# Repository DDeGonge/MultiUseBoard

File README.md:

# MultiUseBoard
The MUB - An ultra-compact, modular processing unit

## What is it?
A tiny, modular, all-in-one processing board. On it's own, it can't do much. But this board can be integrated into just about any other board. All of the mcu pins and power lines are accessible through the low-profile connectors, providing the maximum mcu potential for any project.

## So what makes this better than an Arduino/Blue Pill/Feather?
Well, a few reasons...
- Super compact 32mm x 23mm size
- Powerful Cortex M4 120MHz mcu
- Access to EVERY SINGLE PIN (41 total GPIO)
- Super tiny and low profile board-board connectors
- Onboard 5v and 3v3 regulators (Supports up to 32V input)
- $10 BOM cost at qty 1, $7 at qty 10
- Broken out programming header for easy access

## Cool, I want one!
Great! Then build it yourself :) I hope to sell these boards once the global chip shortage resolves itself, but for now you are on your own!

The gerber files to order the board are found in this repo. Order at your own risk.

A probably up-to-date BOM can be found [here](https://octopart.com/bom-tool/H8oUqADt)

A custom package for kicad exists in the libraries folder, so you can easily integrate the mounting footprint into your own board and simply connect a MUB in the slot.

Godspeed.

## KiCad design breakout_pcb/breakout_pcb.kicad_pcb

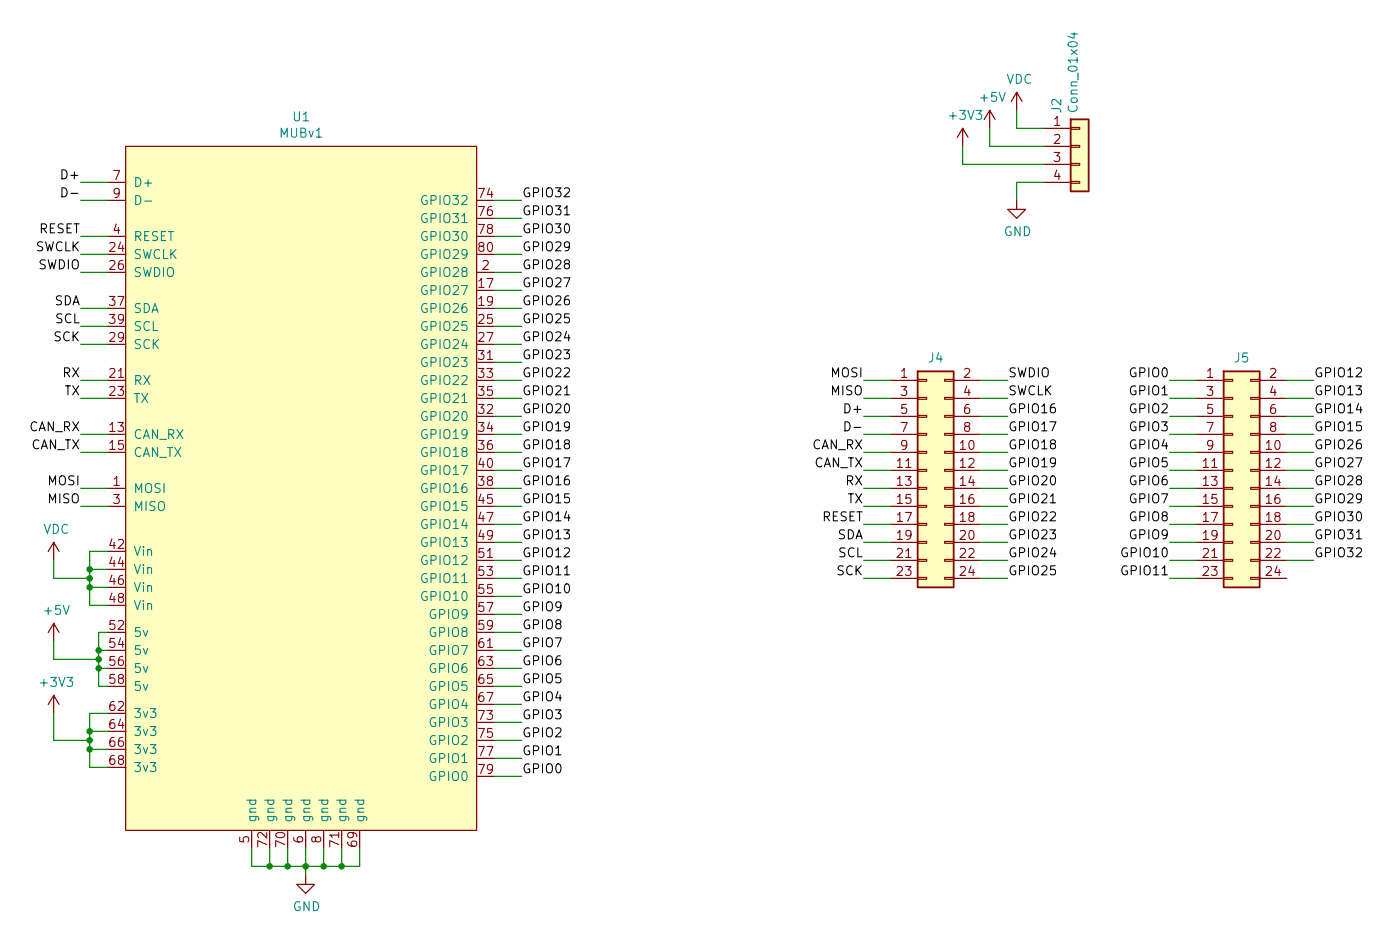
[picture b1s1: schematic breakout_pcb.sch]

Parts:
J2: Conn_01x04; PinSocket_1x04_P2.54mm_Vertical
J4, J5: Conn_02x12_Odd_Even; PinSocket_2x12_P2.54mm_Vertical
U1: MUBv1; MUB_v1

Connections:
+3V3: J2.3, U1.62 (3v3), U1.64 (3v3), U1.66 (3v3), U1.68 (3v3)
+5V: J2.2, U1.52 (5v), U1.54 (5v), U1.56 (5v), U1.58 (5v)
/CAN_RX: J4.9, U1.13 (CAN_RX)
/CAN_TX: J4.11, U1.15 (CAN_TX)
/D+: J4.5, U1.7 (D+)
/D-: J4.7, U1.9 (D-)
/GPIO0: J5.1, U1.79 (GPIO0)
/GPIO1: J5.3, U1.77 (GPIO1)
/GPIO2: J5.5, U1.75 (GPIO2)
/GPIO3: J5.7, U1.73 (GPIO3)
/GPIO4: J5.9, U1.67 (GPIO4)
/GPIO5: J5.11, U1.65 (GPIO5)
/GPIO6: J5.13, U1.63 (GPIO6)
/GPIO7: J5.15, U1.61 (GPIO7)
/GPIO8: J5.17, U1.59 (GPIO8)
/GPIO9: J5.19, U1.57 (GPIO9)
/GPIO10: J5.21, U1.55 (GPIO10)
/GPIO11: J5.23, U1.53 (GPIO11)
/GPIO12: J5.2, U1.51 (GPIO12)
/GPIO13: J5.4, U1.49 (GPIO13)
/GPIO14: J5.6, U1.47 (GPIO14)
/GPIO15: J5.8, U1.45 (GPIO15)
/GPIO16: J4.6, U1.38 (GPIO16)
/GPIO17: J4.8, U1.40 (GPIO17)
/GPIO18: J4.10, U1.36 (GPIO18)
/GPIO19: J4.12, U1.34 (GPIO19)
/GPIO20: J4.14, U1.32 (GPIO20)
/GPIO21: J4.16, U1.35 (GPIO21)
/GPIO22: J4.18, U1.33 (GPIO22)
/GPIO23: J4.20, U1.31 (GPIO23)
/GPIO24: J4.22, U1.27 (GPIO24)
/GPIO25: J4.24, U1.25 (GPIO25)
/GPIO26: J5.10, U1.19 (GPIO26)
/GPIO27: J5.12, U1.17 (GPIO27)
/GPIO28: J5.14, U1.2 (GPIO28)
/GPIO29: J5.16, U1.80 (GPIO29)
/GPIO30: J5.18, U1.78 (GPIO30)
/GPIO31: J5.20, U1.76 (GPIO31)
/GPIO32: J5.22, U1.74 (GPIO32)
/MISO: J4.3, U1.3 (MISO)
/MOSI: J4.1, U1.1 (MOSI)
/RESET: J4.17, U1.4 (RESET)
/RX: J4.13, U1.21 (RX)
/SCK: J4.23, U1.29 (SCK)
/SCL: J4.21, U1.39 (SCL)
/SDA: J4.19, U1.37 (SDA)
/SWCLK: J4.4, U1.24 (SWCLK)
/SWDIO: J4.2, U1.26 (SWDIO)
/TX: J4.15, U1.23 (TX)
GND: J2.4, U1.5 (gnd), U1.6 (gnd), U1.8 (gnd), U1.69 (gnd), U1.70 (gnd), U1.71 (gnd), U1.72 (gnd)
VDC: J2.1, U1.42 (Vin), U1.44 (Vin), U1.46 (Vin), U1.48 (Vin)

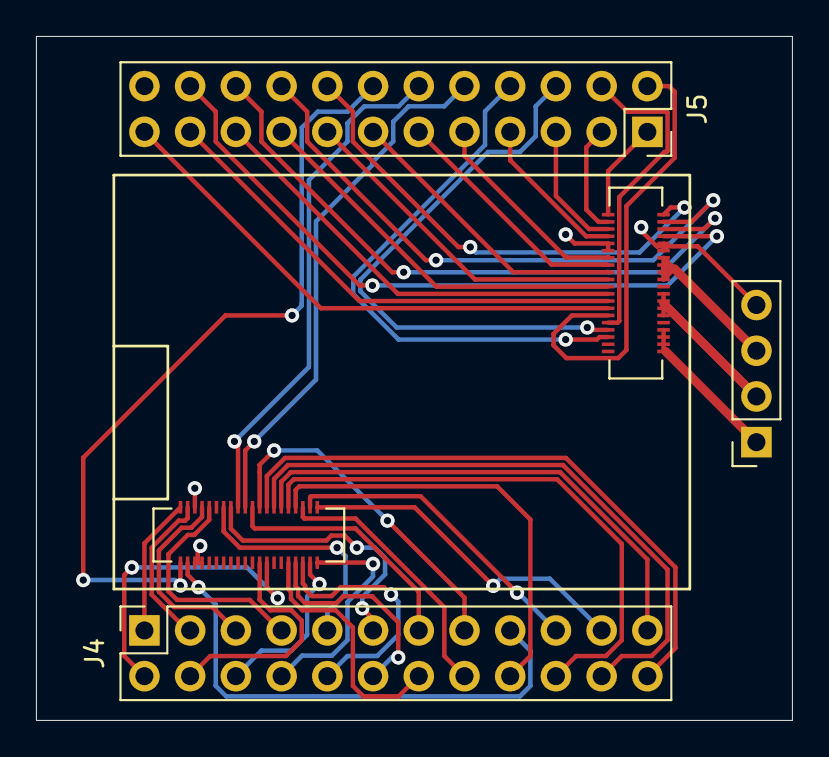
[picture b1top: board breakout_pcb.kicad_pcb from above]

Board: 2 copper layers, 42.0 x 38.0 mm, 4 parts (0 on the bottom side), 51 nets.

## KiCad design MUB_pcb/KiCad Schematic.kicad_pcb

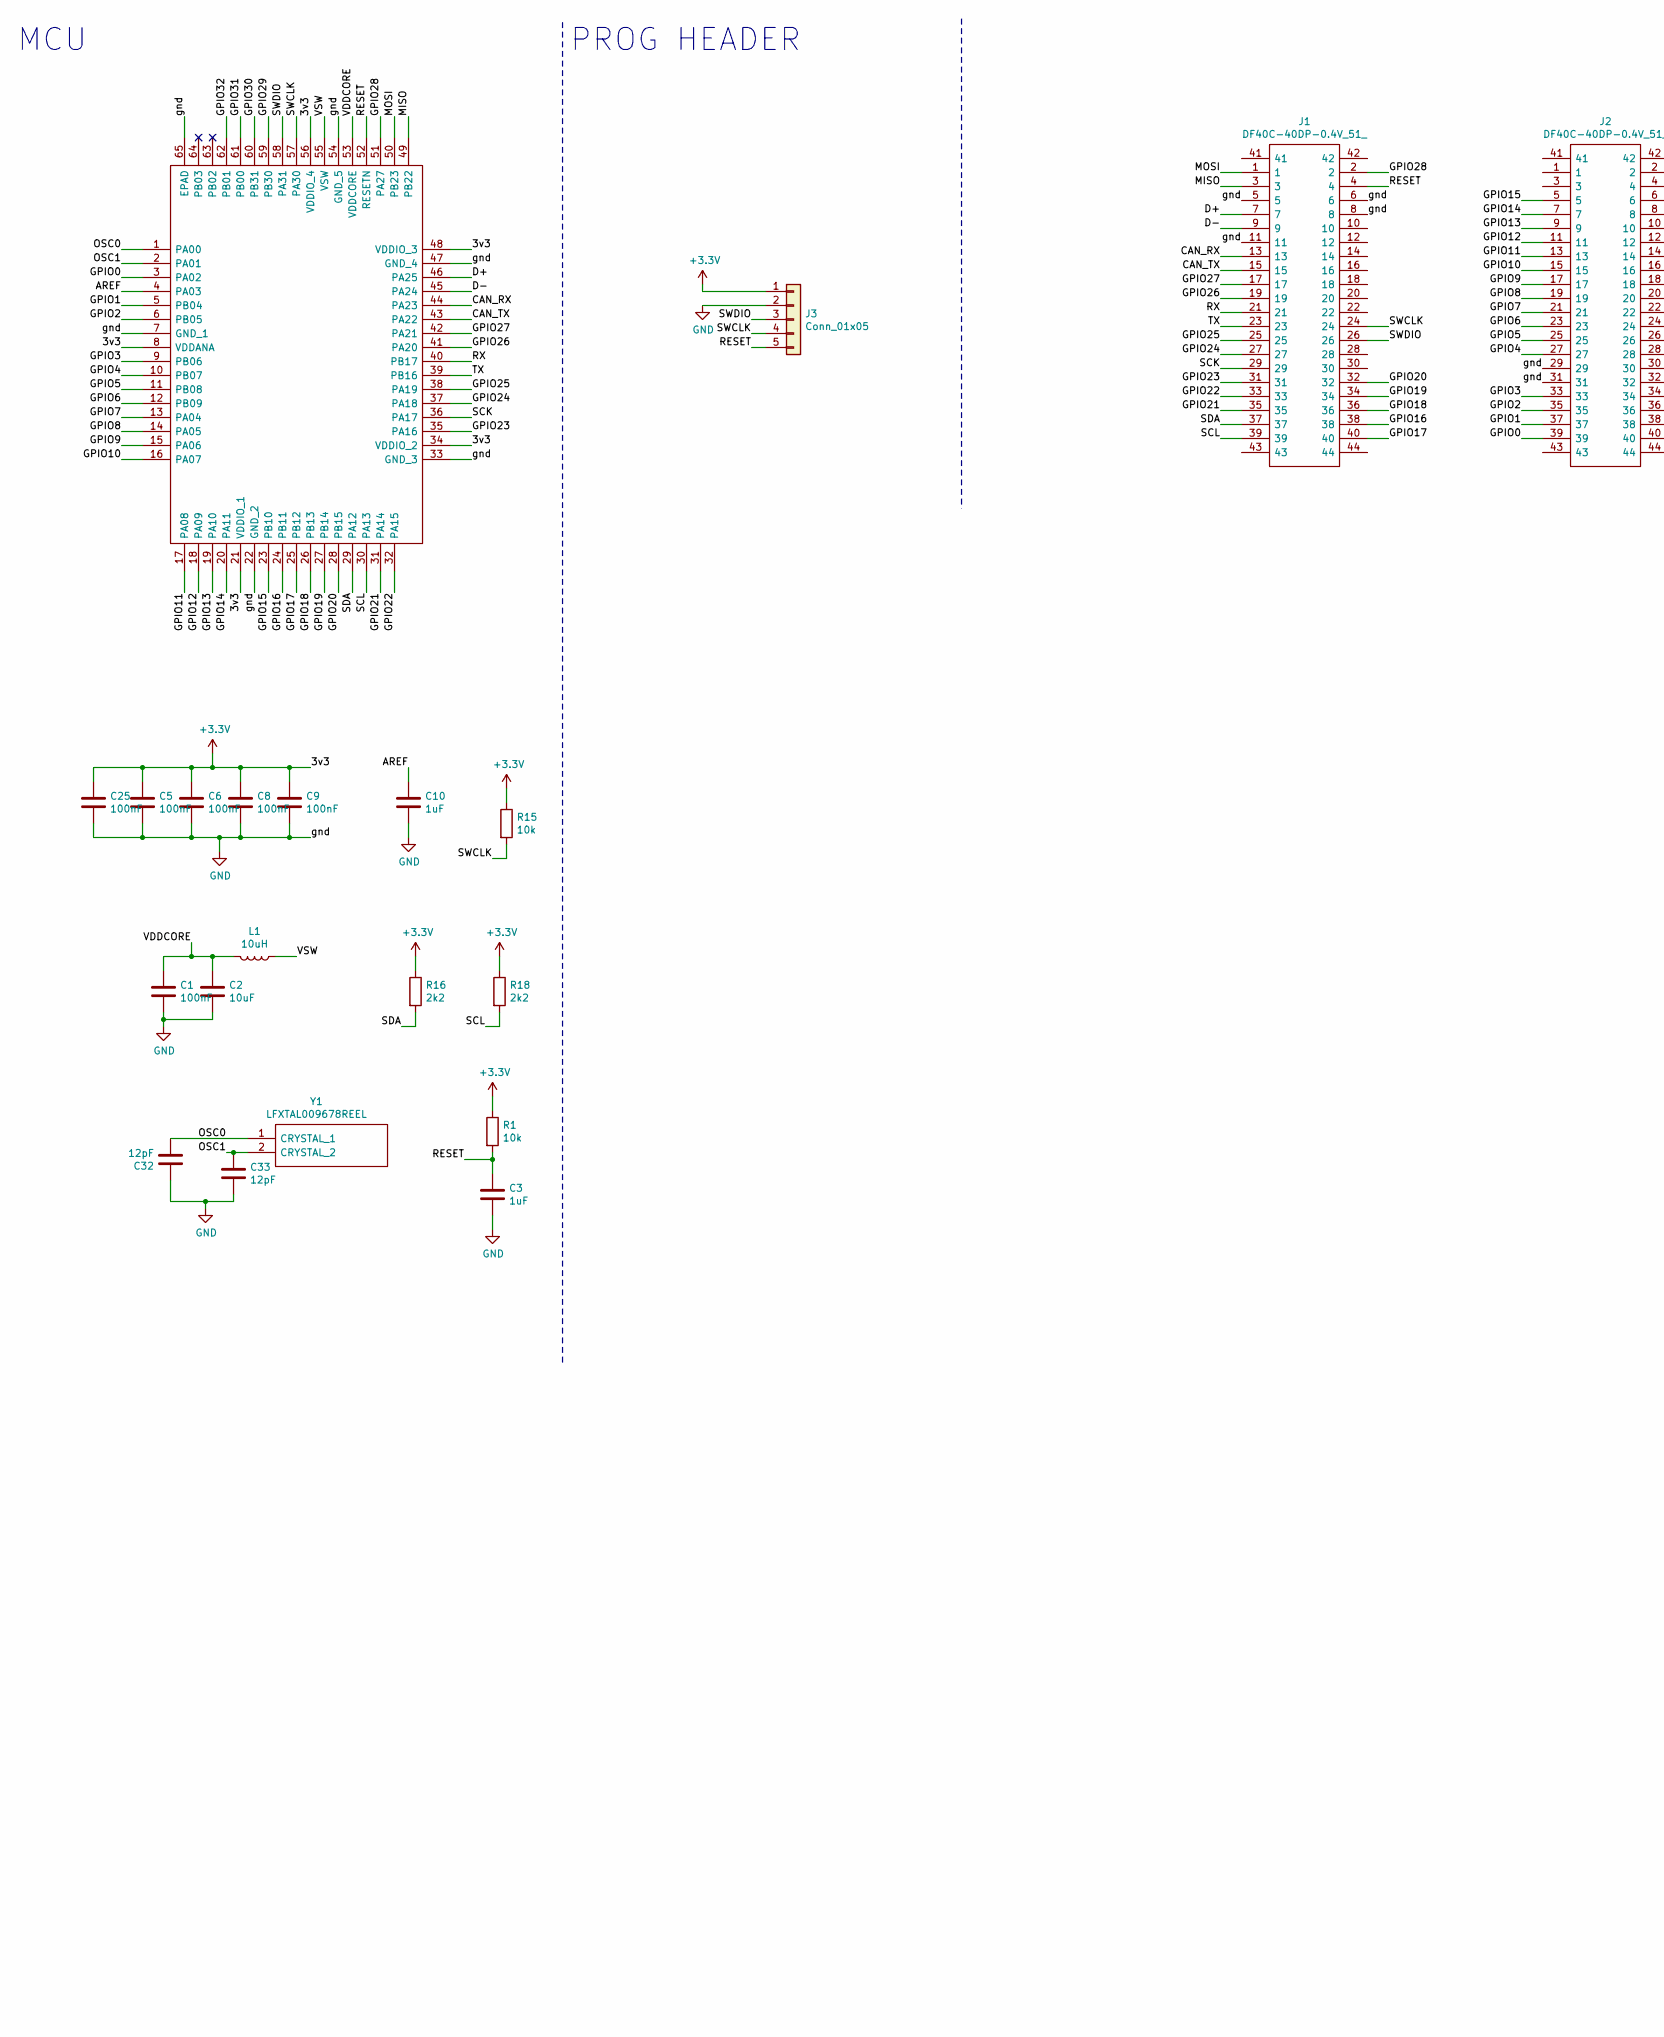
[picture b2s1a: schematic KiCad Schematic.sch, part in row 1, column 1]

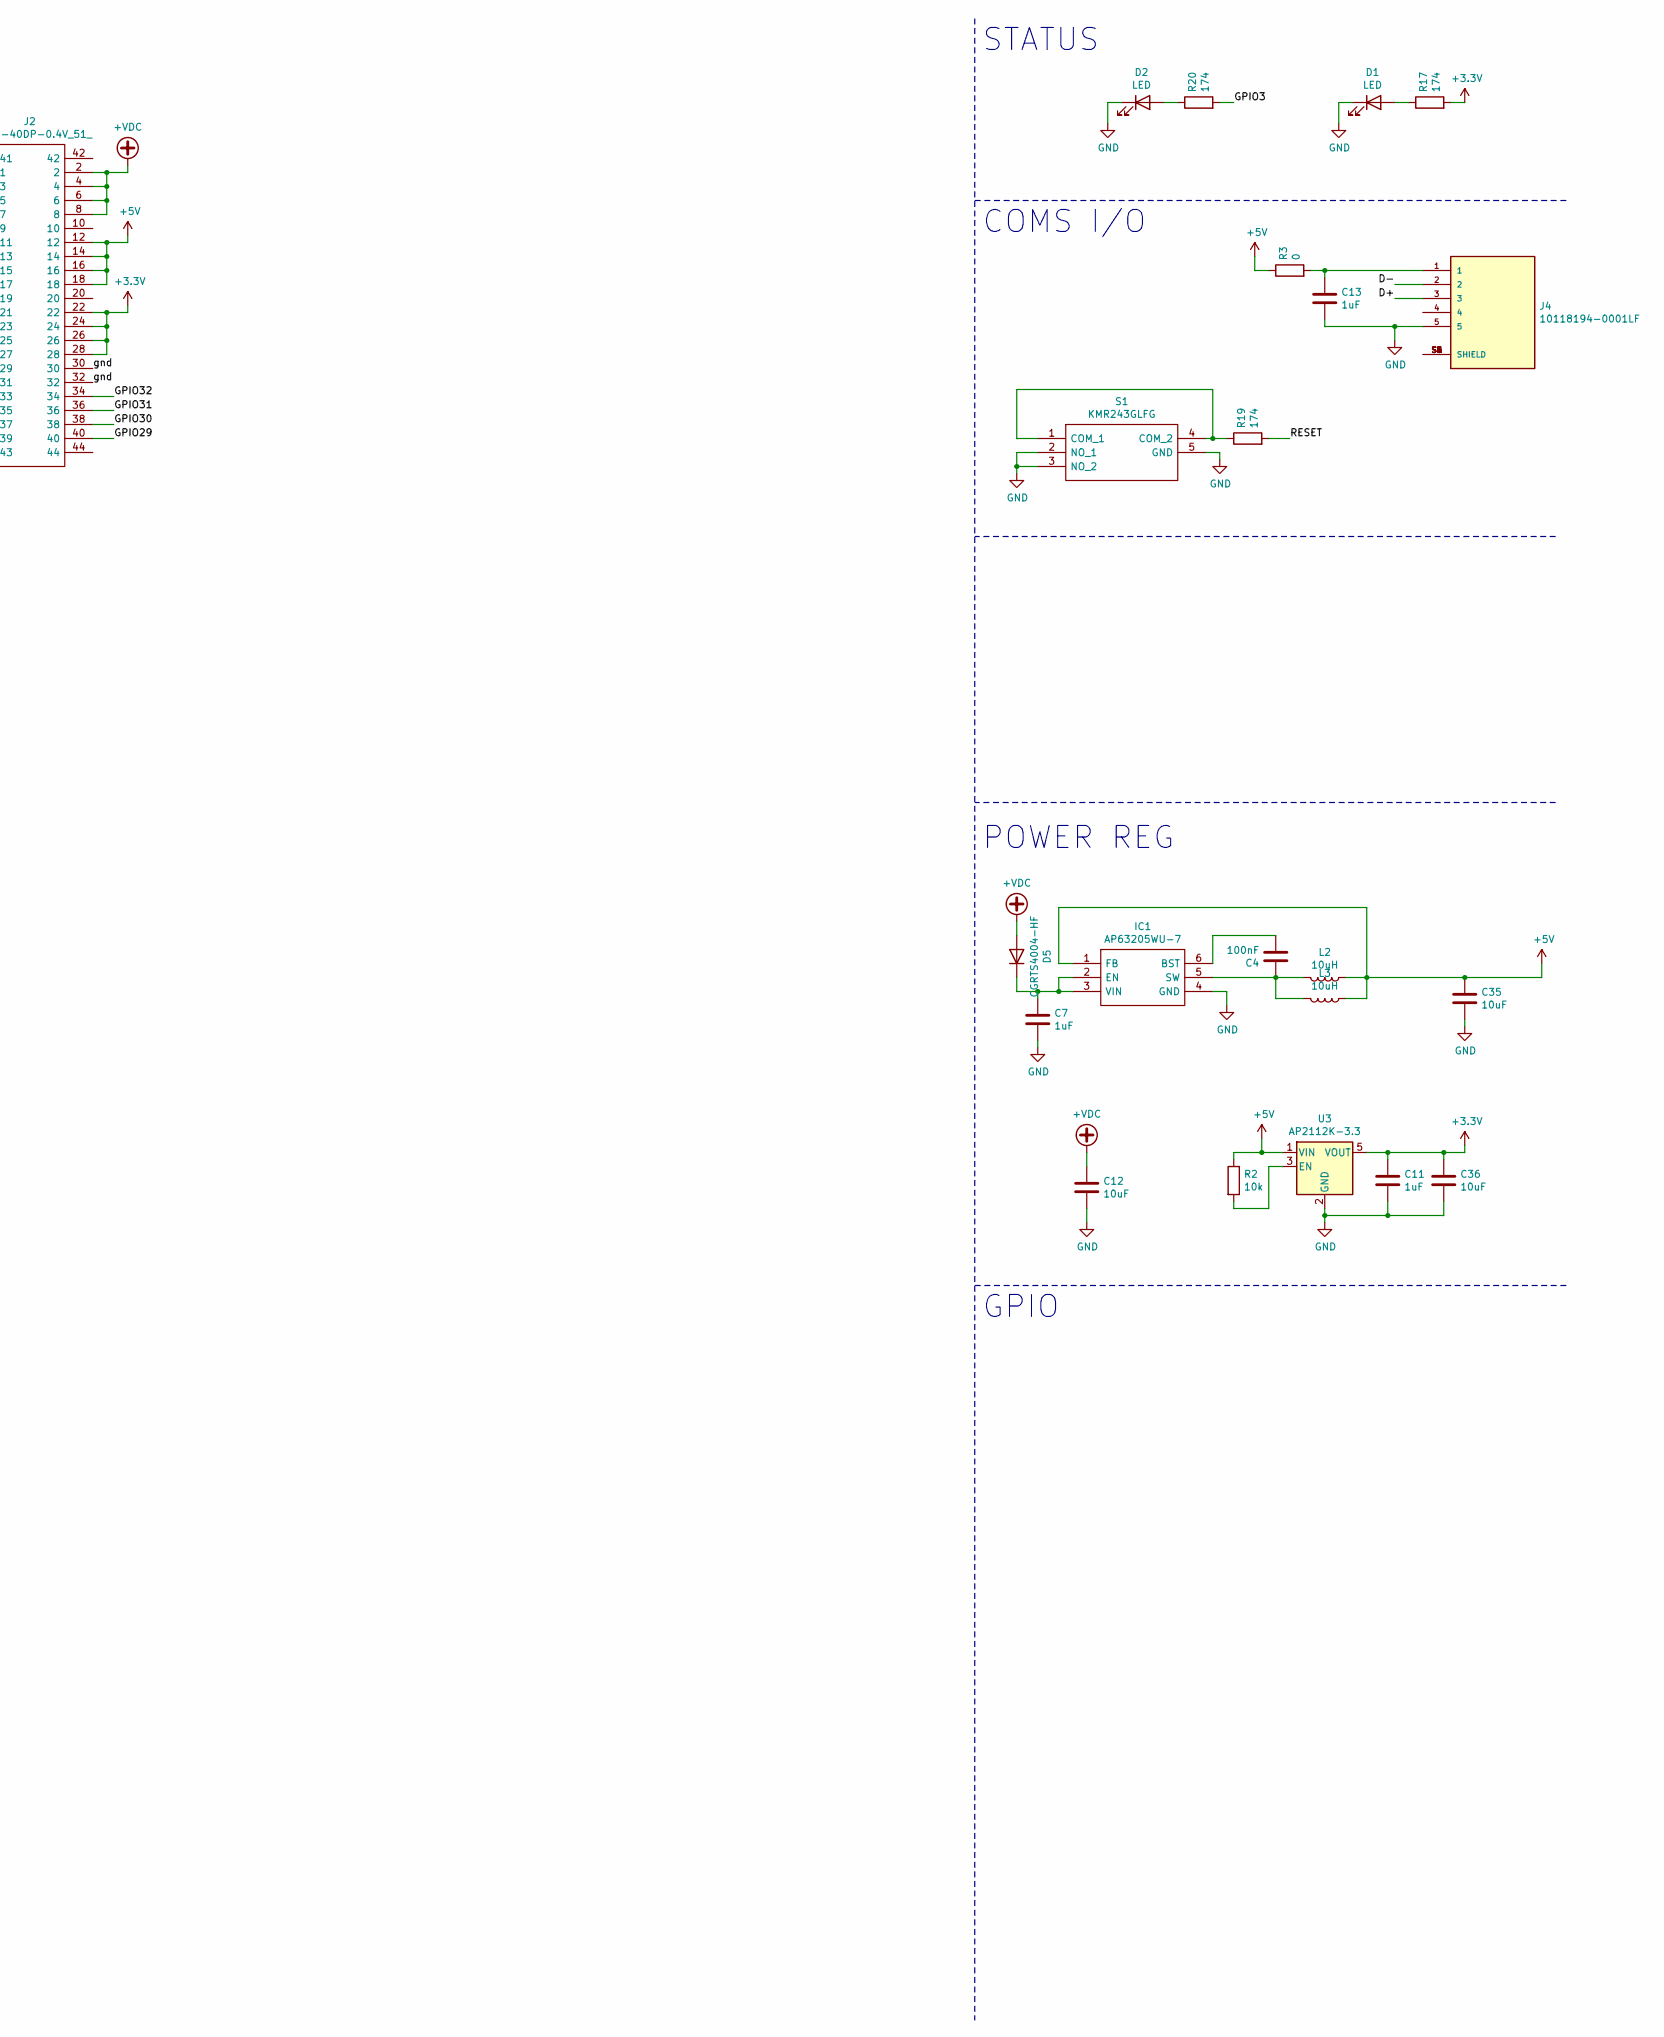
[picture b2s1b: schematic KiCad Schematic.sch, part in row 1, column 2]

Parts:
C1, C4, C5, C6, C8, C9, C25: 100nF; C_0603_1608Metric
C2, C12, C35, C36: 10uF; C_0805_2012Metric
C3, C7, C10, C11, C13: 1uF; C_0603_1608Metric
C32, C33: 12pF; C_0603_1608Metric
D1, D2: LED; LED_0603_1608Metric
D5: CGRTS4004-HF; D_SOD-123F
IC1: AP63205WU-7; SOT95P280X100-6N; Mouser Part Number 621-AP63205WU-7
IC2: ATSAMD51J19A-MU; QFN-64-1EP_9x9mm_P0.5mm_EP6x6mm_ThermalVias; Mouser Part Number 556-ATSAMD51J19AMU
J1, J2: DF40C-40DP-0.4V_51_; DF40C40DP04V51; Manufacturer_Part_Number DF40C-40DP-0.4V(51); Mouser Part Number 798-DF40C40DP0.4V51
J3: Conn_01x05; PinHeader_1x05_P1.27mm_Vertical
J4: 10118194-0001LF; AMPHENOL_10118194-0001LF
L1, L2, L3: 10uH; L_0805_2012Metric
R1, R2, R15: 10k; R_0603_1608Metric
R3: 0; R_0402_1005Metric
R16, R18: 2k2; R_0603_1608Metric
R17, R19, R20: 174; R_0603_1608Metric
S1: KMR243GLFG; KMR421GULCLFS; Mouser Part Number 611-KMR243GLFG
U3: AP2112K-3.3; SOT-23-5
Y1: LFXTAL009678REEL; Mouser Part Number 449-LFXTAL009678REEL

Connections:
+3V3: C5.1, C6.1, C8.1, C9.1, C11.1, C25.1, C36.1, IC2.8 (VDDANA), IC2.21 (VDDIO_1), IC2.34 (VDDIO_2), IC2.48 (VDDIO_3), IC2.56 (VDDIO_4), J2.22, J2.24, J2.26, J2.28, J3.1, R1.1, R15.1, R16.1, R17.2, R18.1, U3.5 (VOUT)
+5V: C35.1, IC1.1 (FB), J2.12, J2.14, J2.16, J2.18, L2.1, L3.1, R2.1, R3.1, U3.1 (VIN)
+VDC: C12.1, D5.2 (A), J2.2, J2.4, J2.6, J2.8
/AREF: C10.1, IC2.4 (PA03)
/CAN_RX: IC2.44 (PA23), J1.13
/CAN_TX: IC2.43 (PA22), J1.15
/D+: IC2.46 (PA25), J1.7, J4.3
/D-: IC2.45 (PA24), J1.9, J4.2
/GPIO0: IC2.3 (PA02), J2.39
/GPIO1: IC2.5 (PB04), J2.37
/GPIO2: IC2.6 (PB05), J2.35
/GPIO3: IC2.9 (PB06), J2.33, R20.2
/GPIO4: IC2.10 (PB07), J2.27
/GPIO5: IC2.11 (PB08), J2.25
/GPIO6: IC2.12 (PB09), J2.23
/GPIO7: IC2.13 (PA04), J2.21
/GPIO8: IC2.14 (PA05), J2.19
/GPIO9: IC2.15 (PA06), J2.17
/GPIO10: IC2.16 (PA07), J2.15
/GPIO11: IC2.17 (PA08), J2.13
/GPIO12: IC2.18 (PA09), J2.11
/GPIO13: IC2.19 (PA10), J2.9
/GPIO14: IC2.20 (PA11), J2.7
/GPIO15: IC2.23 (PB10), J2.5
/GPIO16: IC2.24 (PB11), J1.38
/GPIO17: IC2.25 (PB12), J1.40
/GPIO18: IC2.26 (PB13), J1.36
/GPIO19: IC2.27 (PB14), J1.34
/GPIO20: IC2.28 (PB15), J1.32
/GPIO21: IC2.31 (PA14), J1.35
/GPIO22: IC2.32 (PA15), J1.33
/GPIO23: IC2.35 (PA16), J1.31
/GPIO24: IC2.37 (PA18), J1.27
/GPIO25: IC2.38 (PA19), J1.25
/GPIO26: IC2.41 (PA20), J1.19
/GPIO27: IC2.42 (PA21), J1.17
/GPIO28: IC2.51 (PA27), J1.2
/GPIO29: IC2.59 (PB30), J2.40
/GPIO30: IC2.60 (PB31), J2.38
/GPIO31: IC2.61 (PB00), J2.36
/GPIO32: IC2.62 (PB01), J2.34
/MISO: IC2.49 (PB22), J1.3
/MOSI: IC2.50 (PB23), J1.1
/OSC0: C32.2, IC2.1 (PA00), Y1.1 (CRYSTAL_1)
/OSC1: C33.1, IC2.2 (PA01), Y1.2 (CRYSTAL_2)
/RESET: C3.1, IC2.52 (RESETN), J1.4, J3.5, R1.2, R19.2
/RX: IC2.40 (PB17), J1.21
/SCK: IC2.36 (PA17), J1.29
/SCL: IC2.30 (PA13), J1.39, R18.2
/SDA: IC2.29 (PA12), J1.37, R16.2
/SWCLK: IC2.57 (PA30), J1.24, J3.4, R15.2
/SWDIO: IC2.58 (PA31), J1.26, J3.3
/TX: IC2.39 (PB16), J1.23
/VDDCORE: C1.1, C2.1, IC2.53 (VDDCORE), L1.2
/VSW: IC2.55 (VSW), L1.1
GND: C1.2, C2.2, C3.2, C5.2, C6.2, C7.2, C8.2, C9.2, C10.2, C11.2, C12.2, C13.2, C25.2, C32.1, C33.2, C35.2, C36.2, D1.1 (K), D2.1 (K), IC1.4 (GND), IC2.7 (GND_1), IC2.22 (GND_2), IC2.33 (GND_3), IC2.47 (GND_4), IC2.54 (GND_5), IC2.65 (EPAD), J1.5, J1.6, J1.8, J1.11, J2.29, J2.30, J2.31, J2.32, J3.2, J4.5, S1.2 (NO_1), S1.3 (NO_2), S1.5 (GND), U3.2 (GND)
unnamed: C4.1, IC1.5 (SW), L2.2, L3.2
unnamed: C4.2, IC1.6 (BST)
unnamed: C7.1, D5.1 (K), IC1.2 (EN), IC1.3 (VIN)
unnamed: C13.1, J4.1, R3.2
unnamed: D1.2 (A), R17.1
unnamed: D2.2 (A), R20.1
unnamed: J4.S1 (SHIELD), J4.S2 (SHIELD), J4.S3 (SHIELD), J4.S4 (SHIELD), J4.S5 (SHIELD), J4.S6 (SHIELD)
unnamed: R2.2, U3.3 (EN)
unnamed: R19.1, S1.1 (COM_1), S1.4 (COM_2)

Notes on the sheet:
GPIO
POWER REG
COMS I/O
STATUS
PROG HEADER
MCU

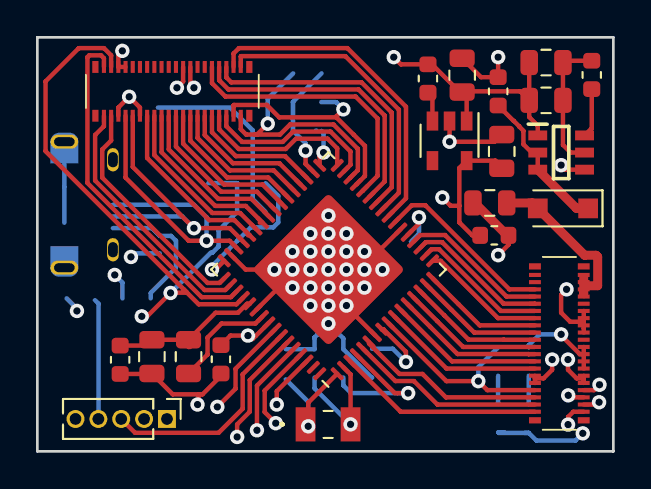
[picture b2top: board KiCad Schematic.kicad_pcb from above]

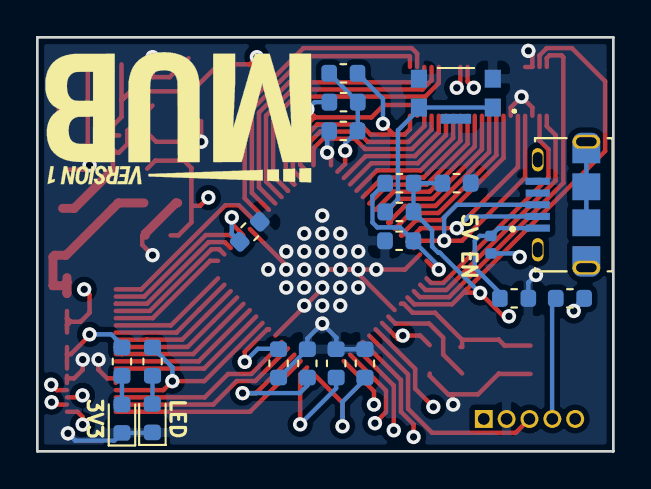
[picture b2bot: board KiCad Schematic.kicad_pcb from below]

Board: 4 copper layers, 32.0 x 23.0 mm, 42 parts (21 on the bottom side), 65 nets.

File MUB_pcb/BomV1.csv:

"Id";"Designator";"Package";"Quantity";"Designation";"Supplier and ref";
1;"J3";"PinHeader_1x05_P1.27mm_Vertical";1;"Conn_01x05";;;
2;"R3";"R_0402_1005Metric";1;"0";;;
3;"G***";"logo_v1";1;"LOGO";;;
4;"C35,C12,C36,C2";"C_0805_2012Metric";4;"10uF";;;
5;"C13,C3,C11,C10,C7";"C_0603_1608Metric";5;"1uF";;;
6;"C8,C25,C9,C6,C5,C4,C1";"C_0603_1608Metric";7;"100nF";;;
7;"R15,R1,R2";"R_0603_1608Metric";3;"10k";;;
8;"J4";"AMPHENOL_10118194-0001LF";1;"10118194-0001LF";;;
9;"IC2";"QFN-64-1EP_9x9mm_P0.5mm_EP6x6mm";1;"ATSAMD51J19A-MU";;;
10;"J2,J1";"DF40C40DP04V51";2;"DF40C-40DP-0.4V_51_";;;
11;"S1";"KMR421GULCLFS";1;"KMR243GLFG";;;
12;"R20,R19,R17";"R_0603_1608Metric";3;"174";;;
13;"D2,D1";"LED_0603_1608Metric";2;"LED";;;
14;"Y1";"LFXTAL009678REEL";1;"LFXTAL009678REEL";;;
15;"U3";"SOT-23-5";1;"AP2112K-3.3";;;
16;"R18,R16";"R_0603_1608Metric";2;"2k2";;;
17;"L3,L2,L1";"L_0805_2012Metric";3;"10uH";;;
18;"IC1";"SOT95P280X100-6N";1;"AP63205WU-7";;;
19;"D5";"D_SOD-123F";1;"CGRTS4004-HF";;;
20;"C33,C32";"C_0603_1608Metric";2;"12pF";;;

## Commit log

2021-10-19 push MUB v1.0 plus accessory boards
2021-10-31 export bom and update readme
2021-11-01 start arduino package
2021-11-01 add mub package v1.0.0
2021-11-01 update package data
2021-11-01 version bump
2021-11-01 new hash type
2021-11-01 try again
2021-11-14 bugfix, missing commas
2022-10-06 fix package
2022-10-06 fix hash
2022-10-06 fix package url
2022-10-06 fix package url...again
2022-10-06 arduino version bump
